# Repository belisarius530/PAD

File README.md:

# PAD
An "alarm" circuit, inspired by David Garges

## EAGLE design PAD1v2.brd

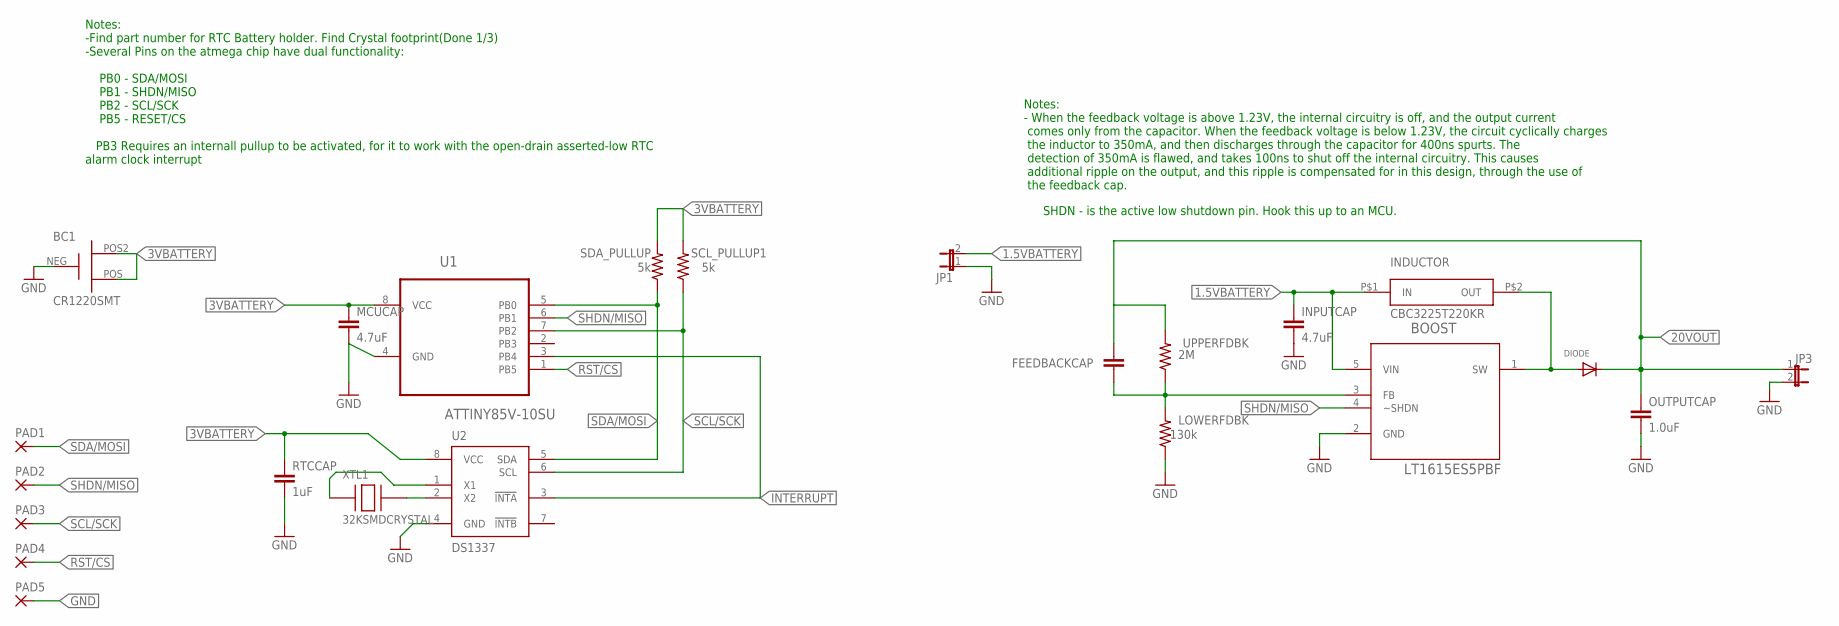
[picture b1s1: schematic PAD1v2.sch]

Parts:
BC1: CR1220SMT; 3000TR
BOOST: LT1615ES5PBF; SOT95P280X145-5N
DIODE: DIODESOD-123; SOD-123
FEEDBACKCAP: 4.7pF; 1206
INDUCTOR: CBC3225T220KR; 1210
INPUTCAP: 4.7uF; 1206
JP1: JUMPER-2PTH; 1X02
JP3: JUMPER-2PTH_LOCK; 1X02_LOCK
LOWERFDBK: 130k; 1206
MCUCAP: 4.7uF; 1206
OUTPUTCAP: 1.0uF; 1206
PAD1, PAD2, PAD3, PAD4, PAD5: 1,6/0,8
RTCCAP: 1uF; 1206
SCL_PULLUP1: 5k; 1206
SDA_PULLUP: 5k; 1206
U1: ATTINY85V-10SU; SOIC127P798X216-8N
U2: DS1337; UMAX8
UPPERFDBK: 2M; 1206
XTL1: 32KSMDCRYSTAL; 4-SMD

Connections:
1.5VBATTERY: BOOST.5 (VIN), INDUCTOR.P$1 (IN), INPUTCAP.1, JP1.2
3VBATTERY: BC1.POS, BC1.POS2, MCUCAP.1, RTCCAP.1, SCL_PULLUP1.2, SDA_PULLUP.2, U1.8 (VCC), U2.8 (VCC)
20VOUT: DIODE.C, FEEDBACKCAP.1, JP3.1, OUTPUTCAP.1, UPPERFDBK.2
GND: BC1.NEG, BOOST.2 (GND), INPUTCAP.2, JP1.1, JP3.2, LOWERFDBK.1, MCUCAP.2, OUTPUTCAP.2, PAD5.1, RTCCAP.2, U1.4 (GND), U2.4 (GND)
INTERRUPT: U1.3 (PB4), U2.3 (!INTA)
unnamed: BOOST.1 (SW), DIODE.A, INDUCTOR.P$2 (OUT)
unnamed: BOOST.3 (FB), FEEDBACKCAP.2, LOWERFDBK.2, UPPERFDBK.1
unnamed: U2.2 (X2), XTL1.XTAL2
unnamed: U2.1 (X1), XTL1.XTAL1
RST/CS: PAD4.1, U1.1 (PB5)
SCL/SCK: PAD3.1, SCL_PULLUP1.1, U1.7 (PB2), U2.6 (SCL)
SDA/MOSI: PAD1.1, SDA_PULLUP.1, U1.5 (PB0), U2.5 (SDA)
SHDN/MISO: BOOST.4 (~SHDN), PAD2.1, U1.6 (PB1)

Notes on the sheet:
Notes: - When the feedback voltage is above 1.23V, the internal circuitry is off, and the output current comes only from the capacitor. When the feedback voltage is below 1.23V, the circuit cyclically charges the inductor to 350mA, and then discharges through the capacitor for 400ns spurts. The det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
SHDN - is the active low shutdown pin. Hook this up to an MCU.
Notes: -Find part number for RTC Battery holder. Find Crystal footprint(Done 1/3) -Several Pins on the atmega chip have dual functionality: PB0 - SDA/MOSI PB1 - SHDN/MISO PB2 - SCL/SCK PB5 - RESET/CS PB3 Requires an internall pullup to be activated, for it to work with the open-drain asserted-low R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

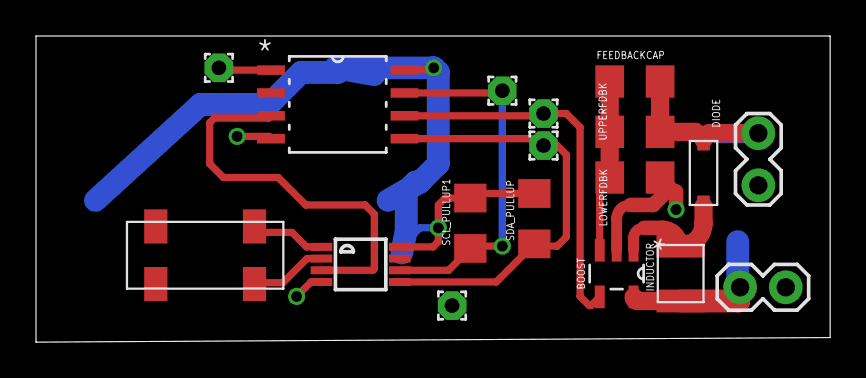
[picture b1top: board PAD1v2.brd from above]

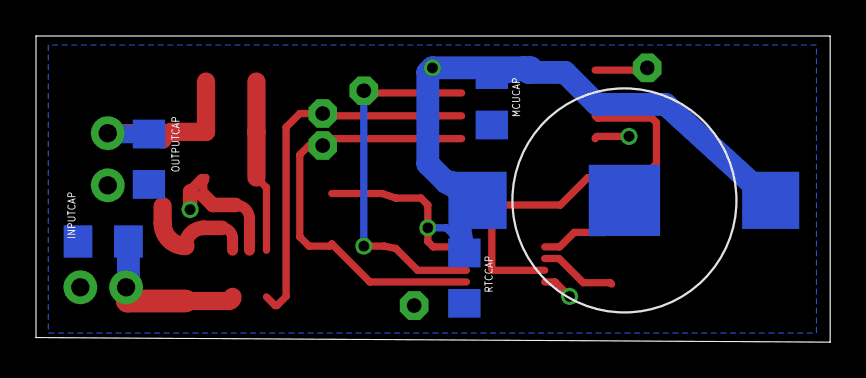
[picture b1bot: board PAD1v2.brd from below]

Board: 2 copper layers, 44.1 x 17.0 mm, 23 parts (5 on the bottom side), 13 nets.

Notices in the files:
parts and their libraries:
SparkFun-Retired: Licensing:Creative Commons ShareAlike 4.0 International - https://creativecommons.org/licenses/by-sa/4.0
